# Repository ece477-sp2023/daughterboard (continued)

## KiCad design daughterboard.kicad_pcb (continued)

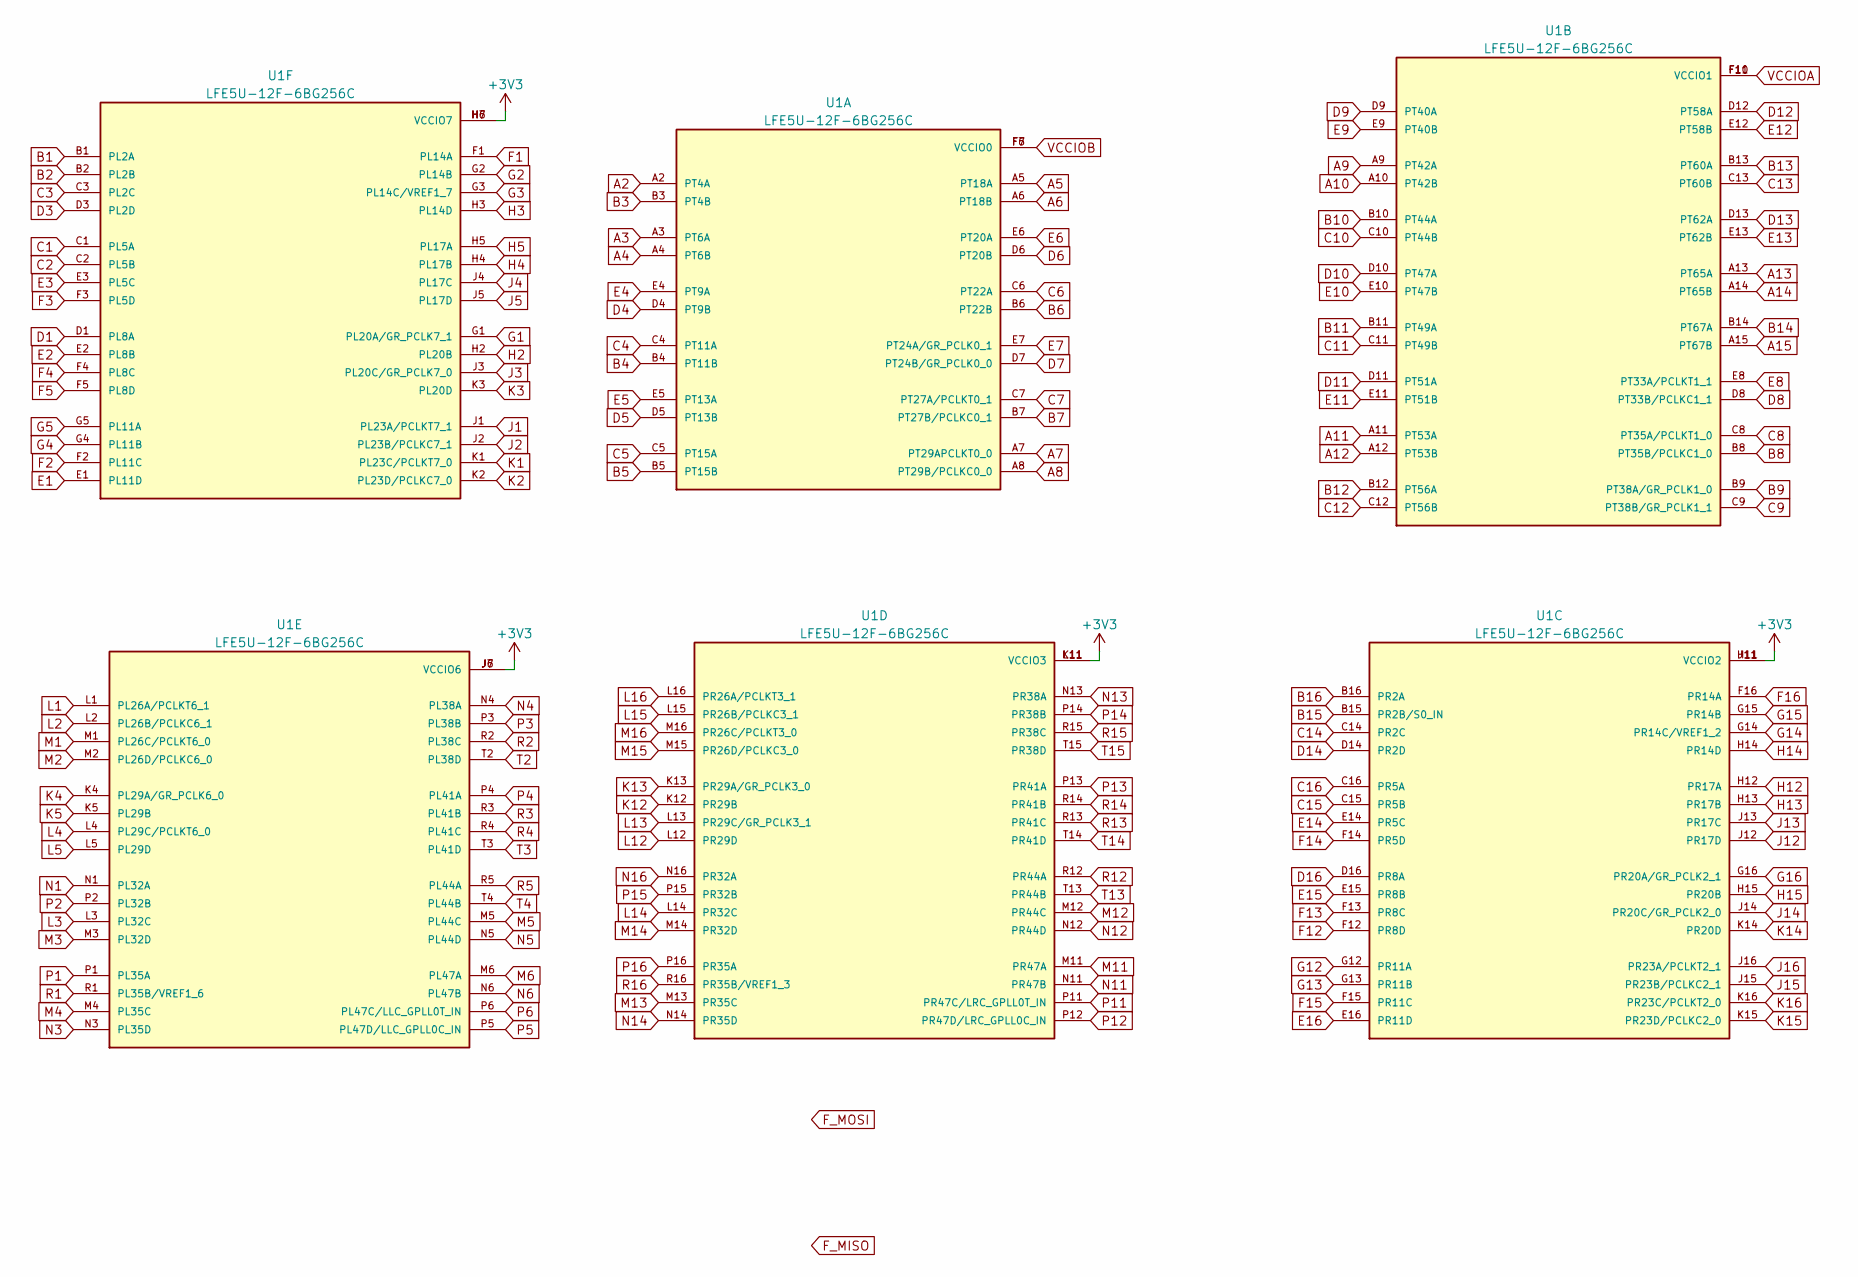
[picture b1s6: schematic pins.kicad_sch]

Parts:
U1: LFE5U-12F-6BG256C; BGA256C80P16X16_1400X1400X170; PARTREV 2.0

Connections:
A2: U1.A2 (PT4A); also elsewhere on the board
A3: U1.A3 (PT6A); also elsewhere on the board
A4: U1.A4 (PT6B); also elsewhere on the board
A5: U1.A5 (PT18A); also elsewhere on the board
A6: U1.A6 (PT18B); also elsewhere on the board
A7: U1.A7 (PT29APCLKT0_0); also elsewhere on the board
A8: U1.A8 (PT29B/PCLKC0_0); also elsewhere on the board
A9: U1.A9 (PT42A); also elsewhere on the board
A10: U1.A10 (PT42B); also elsewhere on the board
A11: U1.A11 (PT53A); also elsewhere on the board
A12: U1.A12 (PT53B); also elsewhere on the board
A13: U1.A13 (PT65A); also elsewhere on the board
A14: U1.A14 (PT65B); also elsewhere on the board
A15: U1.A15 (PT67B); also elsewhere on the board
B1: U1.B1 (PL2A); also elsewhere on the board
B2: U1.B2 (PL2B); also elsewhere on the board
B3: U1.B3 (PT4B); also elsewhere on the board
B4: U1.B4 (PT11B); also elsewhere on the board
B5: U1.B5 (PT15B); also elsewhere on the board
B6: U1.B6 (PT22B); also elsewhere on the board
B7: U1.B7 (PT27B/PCLKC0_1); also elsewhere on the board
B8: U1.B8 (PT35B/PCLKC1_0); also elsewhere on the board
B9: U1.B9 (PT38A/GR_PCLK1_0); also elsewhere on the board
B10: U1.B10 (PT44A); also elsewhere on the board
B11: U1.B11 (PT49A); also elsewhere on the board
B12: U1.B12 (PT56A); also elsewhere on the board
B13: U1.B13 (PT60A); also elsewhere on the board
B14: U1.B14 (PT67A); also elsewhere on the board
B15: U1.B15 (PR2B/S0_IN); also elsewhere on the board
B16: U1.B16 (PR2A); also elsewhere on the board
C1: U1.C1 (PL5A); also elsewhere on the board
C2: U1.C2 (PL5B); also elsewhere on the board
C3: U1.C3 (PL2C); also elsewhere on the board
C4: U1.C4 (PT11A); also elsewhere on the board
C5: U1.C5 (PT15A); also elsewhere on the board
C6: U1.C6 (PT22A); also elsewhere on the board
C7: U1.C7 (PT27A/PCLKT0_1); also elsewhere on the board
C8: U1.C8 (PT35A/PCLKT1_0); also elsewhere on the board
C9: U1.C9 (PT38B/GR_PCLK1_1); also elsewhere on the board
C10: U1.C10 (PT44B); also elsewhere on the board
C11: U1.C11 (PT49B); also elsewhere on the board
C12: U1.C12 (PT56B); also elsewhere on the board
C13: U1.C13 (PT60B); also elsewhere on the board
C14: U1.C14 (PR2C); also elsewhere on the board
C15: U1.C15 (PR5B); also elsewhere on the board
C16: U1.C16 (PR5A); also elsewhere on the board
D1: U1.D1 (PL8A); also elsewhere on the board
D3: U1.D3 (PL2D); also elsewhere on the board
D4: U1.D4 (PT9B); also elsewhere on the board
D5: U1.D5 (PT13B); also elsewhere on the board
D6: U1.D6 (PT20B); also elsewhere on the board
D7: U1.D7 (PT24B/GR_PCLK0_0); also elsewhere on the board
D8: U1.D8 (PT33B/PCLKC1_1); also elsewhere on the board
D9: U1.D9 (PT40A); also elsewhere on the board
D10: U1.D10 (PT47A); also elsewhere on the board
D11: U1.D11 (PT51A); also elsewhere on the board
D12: U1.D12 (PT58A); also elsewhere on the board
D13: U1.D13 (PT62A); also elsewhere on the board
D14: U1.D14 (PR2D); also elsewhere on the board
D16: U1.D16 (PR8A); also elsewhere on the board
E1: U1.E1 (PL11D); also elsewhere on the board
E2: U1.E2 (PL8B); also elsewhere on the board
E3: U1.E3 (PL5C); also elsewhere on the board
E4: U1.E4 (PT9A); also elsewhere on the board
E5: U1.E5 (PT13A); also elsewhere on the board
E6: U1.E6 (PT20A); also elsewhere on the board
E7: U1.E7 (PT24A/GR_PCLK0_1); also elsewhere on the board
E8: U1.E8 (PT33A/PCLKT1_1); also elsewhere on the board
E9: U1.E9 (PT40B); also elsewhere on the board
E10: U1.E10 (PT47B); also elsewhere on the board
E11: U1.E11 (PT51B); also elsewhere on the board
E12: U1.E12 (PT58B); also elsewhere on the board
E13: U1.E13 (PT62B); also elsewhere on the board
E14: U1.E14 (PR5C); also elsewhere on the board
E15: U1.E15 (PR8B); also elsewhere on the board
E16: U1.E16 (PR11D); also elsewhere on the board
F1: U1.F1 (PL14A); also elsewhere on the board
F2: U1.F2 (PL11C); also elsewhere on the board
F3: U1.F3 (PL5D); also elsewhere on the board
F4: U1.F4 (PL8C); also elsewhere on the board
F5: U1.F5 (PL8D); also elsewhere on the board
F12: U1.F12 (PR8D); also elsewhere on the board
F13: U1.F13 (PR8C); also elsewhere on the board
F14: U1.F14 (PR5D); also elsewhere on the board
F15: U1.F15 (PR11C); also elsewhere on the board
F16: U1.F16 (PR14A); also elsewhere on the board
G1: U1.G1 (PL20A/GR_PCLK7_1); also elsewhere on the board
G2: U1.G2 (PL14B); also elsewhere on the board
G3: U1.G3 (PL14C/VREF1_7); also elsewhere on the board
G4: U1.G4 (PL11B); also elsewhere on the board
G5: U1.G5 (PL11A); also elsewhere on the board
G12: U1.G12 (PR11A); also elsewhere on the board
G13: U1.G13 (PR11B); also elsewhere on the board
G14: U1.G14 (PR14C/VREF1_2); also elsewhere on the board
G15: U1.G15 (PR14B); also elsewhere on the board
G16: U1.G16 (PR20A/GR_PCLK2_1); also elsewhere on the board
H2: U1.H2 (PL20B); also elsewhere on the board
H3: U1.H3 (PL14D); also elsewhere on the board
H4: U1.H4 (PL17B); also elsewhere on the board
H5: U1.H5 (PL17A); also elsewhere on the board
H12: U1.H12 (PR17A); also elsewhere on the board
H13: U1.H13 (PR17B); also elsewhere on the board
H14: U1.H14 (PR14D); also elsewhere on the board
H15: U1.H15 (PR20B); also elsewhere on the board
J1: U1.J1 (PL23A/PCLKT7_1); also elsewhere on the board
J2: U1.J2 (PL23B/PCLKC7_1); also elsewhere on the board
J3: U1.J3 (PL20C/GR_PCLK7_0); also elsewhere on the board
J4: U1.J4 (PL17C); also elsewhere on the board
J5: U1.J5 (PL17D); also elsewhere on the board
J12: U1.J12 (PR17D); also elsewhere on the board
J13: U1.J13 (PR17C); also elsewhere on the board
J14: U1.J14 (PR20C/GR_PCLK2_0); also elsewhere on the board
J15: U1.J15 (PR23B/PCLKC2_1); also elsewhere on the board
J16: U1.J16 (PR23A/PCLKT2_1); also elsewhere on the board
K1: U1.K1 (PL23C/PCLKT7_0); also elsewhere on the board
K2: U1.K2 (PL23D/PCLKC7_0); also elsewhere on the board
K3: U1.K3 (PL20D); also elsewhere on the board
K4: U1.K4 (PL29A/GR_PCLK6_0); also elsewhere on the board
K5: U1.K5 (PL29B); also elsewhere on the board
K12: U1.K12 (PR29B); also elsewhere on the board
K13: U1.K13 (PR29A/GR_PCLK3_0); also elsewhere on the board
K14: U1.K14 (PR20D); also elsewhere on the board
K15: U1.K15 (PR23D/PCLKC2_0); also elsewhere on the board
K16: U1.K16 (PR23C/PCLKT2_0); also elsewhere on the board
L1: U1.L1 (PL26A/PCLKT6_1); also elsewhere on the board
L2: U1.L2 (PL26B/PCLKC6_1); also elsewhere on the board
L3: U1.L3 (PL32C); also elsewhere on the board
L4: U1.L4 (PL29C/PCLKT6_0); also elsewhere on the board
L5: U1.L5 (PL29D); also elsewhere on the board
L12: U1.L12 (PR29D); also elsewhere on the board
L13: U1.L13 (PR29C/GR_PCLK3_1); also elsewhere on the board
L14: U1.L14 (PR32C); also elsewhere on the board
L15: U1.L15 (PR26B/PCLKC3_1); also elsewhere on the board
L16: U1.L16 (PR26A/PCLKT3_1); also elsewhere on the board
M1: U1.M1 (PL26C/PCLKT6_0); also elsewhere on the board
M2: U1.M2 (PL26D/PCLKC6_0); also elsewhere on the board
M3: U1.M3 (PL32D); also elsewhere on the board
M4: U1.M4 (PL35C); also elsewhere on the board
M5: U1.M5 (PL44C); also elsewhere on the board
M6: U1.M6 (PL47A); also elsewhere on the board
M11: U1.M11 (PR47A); also elsewhere on the board
M12: U1.M12 (PR44C); also elsewhere on the board
M13: U1.M13 (PR35C); also elsewhere on the board
M14: U1.M14 (PR32D); also elsewhere on the board
M15: U1.M15 (PR26D/PCLKC3_0); also elsewhere on the board
M16: U1.M16 (PR26C/PCLKT3_0); also elsewhere on the board
N1: U1.N1 (PL32A); also elsewhere on the board
N3: U1.N3 (PL35D); also elsewhere on the board
N4: U1.N4 (PL38A); also elsewhere on the board
N5: U1.N5 (PL44D); also elsewhere on the board
N6: U1.N6 (PL47B); also elsewhere on the board
N11: U1.N11 (PR47B); also elsewhere on the board
N12: U1.N12 (PR44D); also elsewhere on the board
N13: U1.N13 (PR38A); also elsewhere on the board
N14: U1.N14 (PR35D); also elsewhere on the board
N16: U1.N16 (PR32A); also elsewhere on the board
P1: U1.P1 (PL35A); also elsewhere on the board
P2: U1.P2 (PL32B); also elsewhere on the board
P3: U1.P3 (PL38B); also elsewhere on the board
P4: U1.P4 (PL41A); also elsewhere on the board
P5: U1.P5 (PL47D/LLC_GPLL0C_IN); also elsewhere on the board
P6: U1.P6 (PL47C/LLC_GPLL0T_IN); also elsewhere on the board
P11: U1.P11 (PR47C/LRC_GPLL0T_IN); also elsewhere on the board
P12: U1.P12 (PR47D/LRC_GPLL0C_IN); also elsewhere on the board
P13: U1.P13 (PR41A); also elsewhere on the board
P14: U1.P14 (PR38B); also elsewhere on the board
P15: U1.P15 (PR32B); also elsewhere on the board
P16: U1.P16 (PR35A); also elsewhere on the board
R1: U1.R1 (PL35B/VREF1_6); also elsewhere on the board
R2: U1.R2 (PL38C); also elsewhere on the board
R3: U1.R3 (PL41B); also elsewhere on the board
R4: U1.R4 (PL41C); also elsewhere on the board
R5: U1.R5 (PL44A); also elsewhere on the board
R12: U1.R12 (PR44A); also elsewhere on the board
R13: U1.R13 (PR41C); also elsewhere on the board
R14: U1.R14 (PR41B); also elsewhere on the board
R15: U1.R15 (PR38C); also elsewhere on the board
R16: U1.R16 (PR35B/VREF1_3); also elsewhere on the board
T2: U1.T2 (PL38D); also elsewhere on the board
T3: U1.T3 (PL41D); also elsewhere on the board
T4: U1.T4 (PL44B); also elsewhere on the board
T13: U1.T13 (PR44B); also elsewhere on the board
T14: U1.T14 (PR41D); also elsewhere on the board
T15: U1.T15 (PR38D); also elsewhere on the board
VCCIOA: U1.F10 (VCCIO1), U1.F11 (VCCIO1); also elsewhere on the board
VCCIOB: U1.F6 (VCCIO0), U1.F7 (VCCIO0); also elsewhere on the board

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
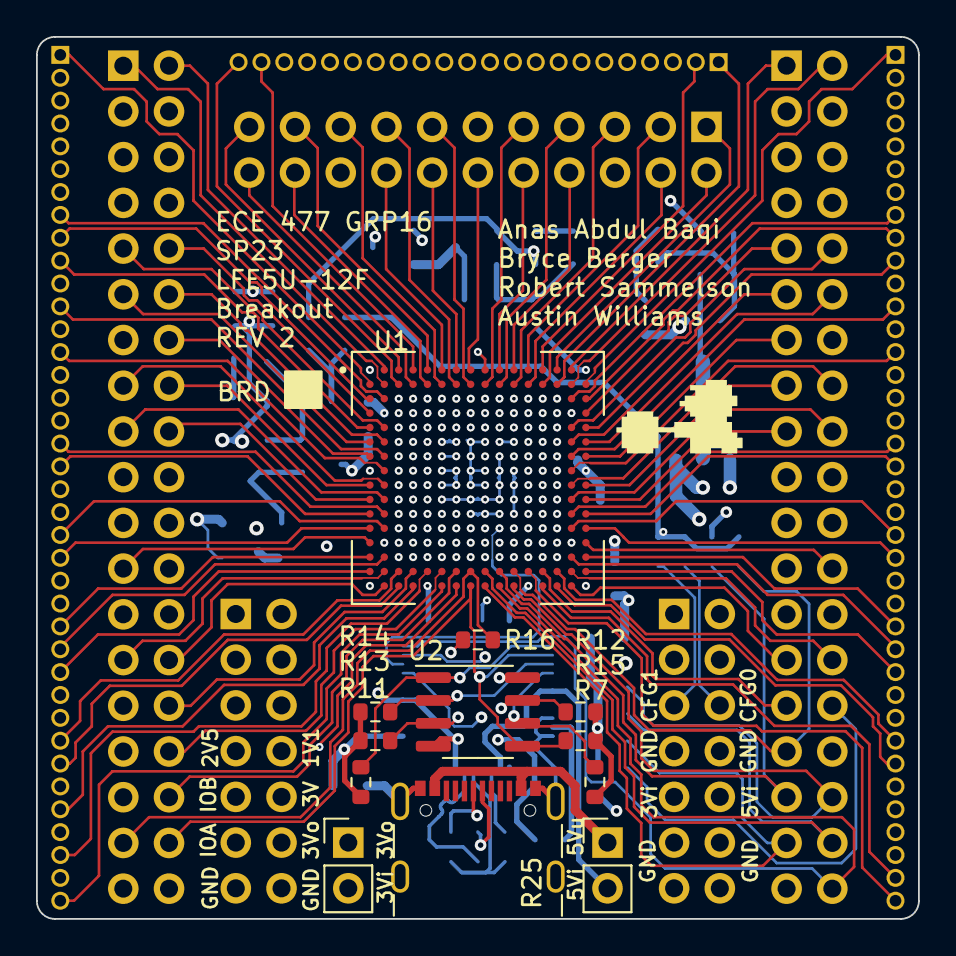
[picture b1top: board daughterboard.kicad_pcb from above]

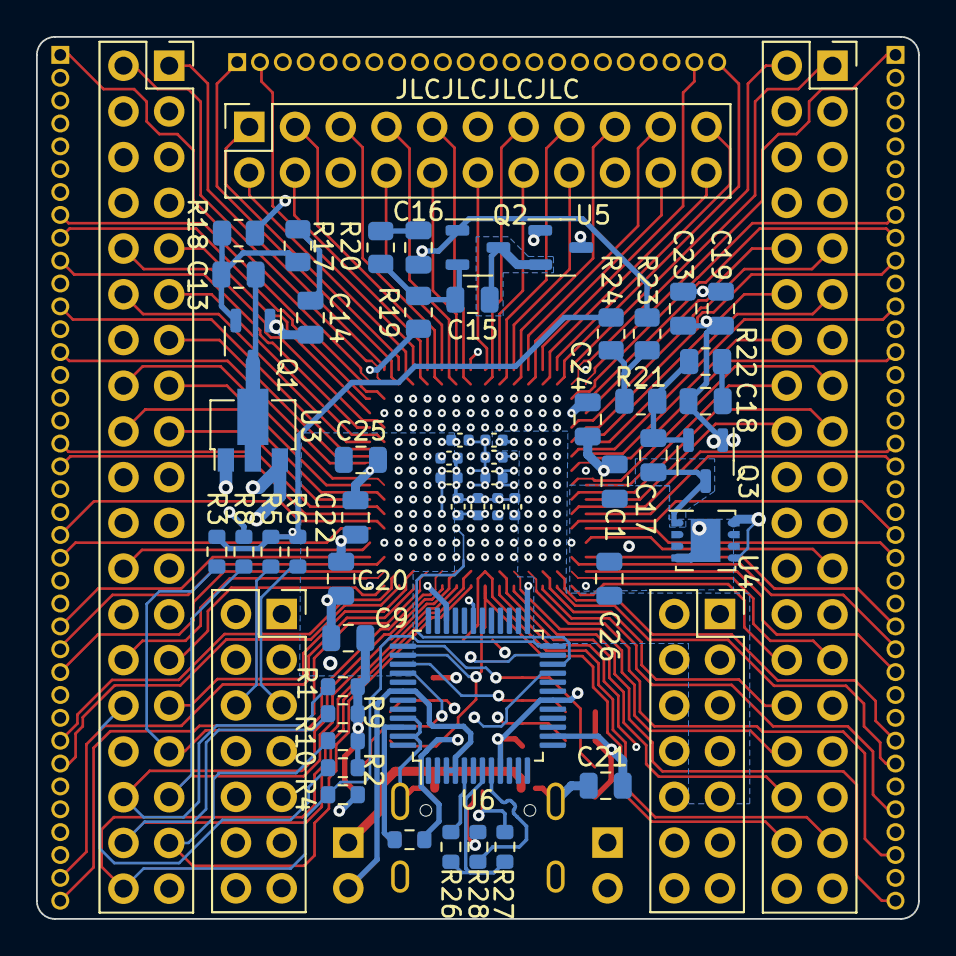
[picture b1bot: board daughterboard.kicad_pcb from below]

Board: 6 copper layers, 49.0 x 49.0 mm, 74 parts (54 on the bottom side), 234 nets.

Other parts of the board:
C9: 10uF; C_0805_2012Metric

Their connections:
GND: C9.2; also elsewhere on the board

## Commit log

2023-02-18 Basic breakout routing complete
2023-02-25 Small routing tweaks, add breakout to schematic
2023-02-26 Route flash + jtag resistors
2023-02-27 Route power
2023-02-27 Move programming pins to 100 mil headers
2023-02-27 Schematic tweaks for readability
2023-03-12 Route power, FTDI chip
2023-03-13 Silkscreen, more power
2023-03-14 Fix hole clearance and add fillet
2023-04-07 Values for slow start circuitry
2023-04-07 Add notes for v3
